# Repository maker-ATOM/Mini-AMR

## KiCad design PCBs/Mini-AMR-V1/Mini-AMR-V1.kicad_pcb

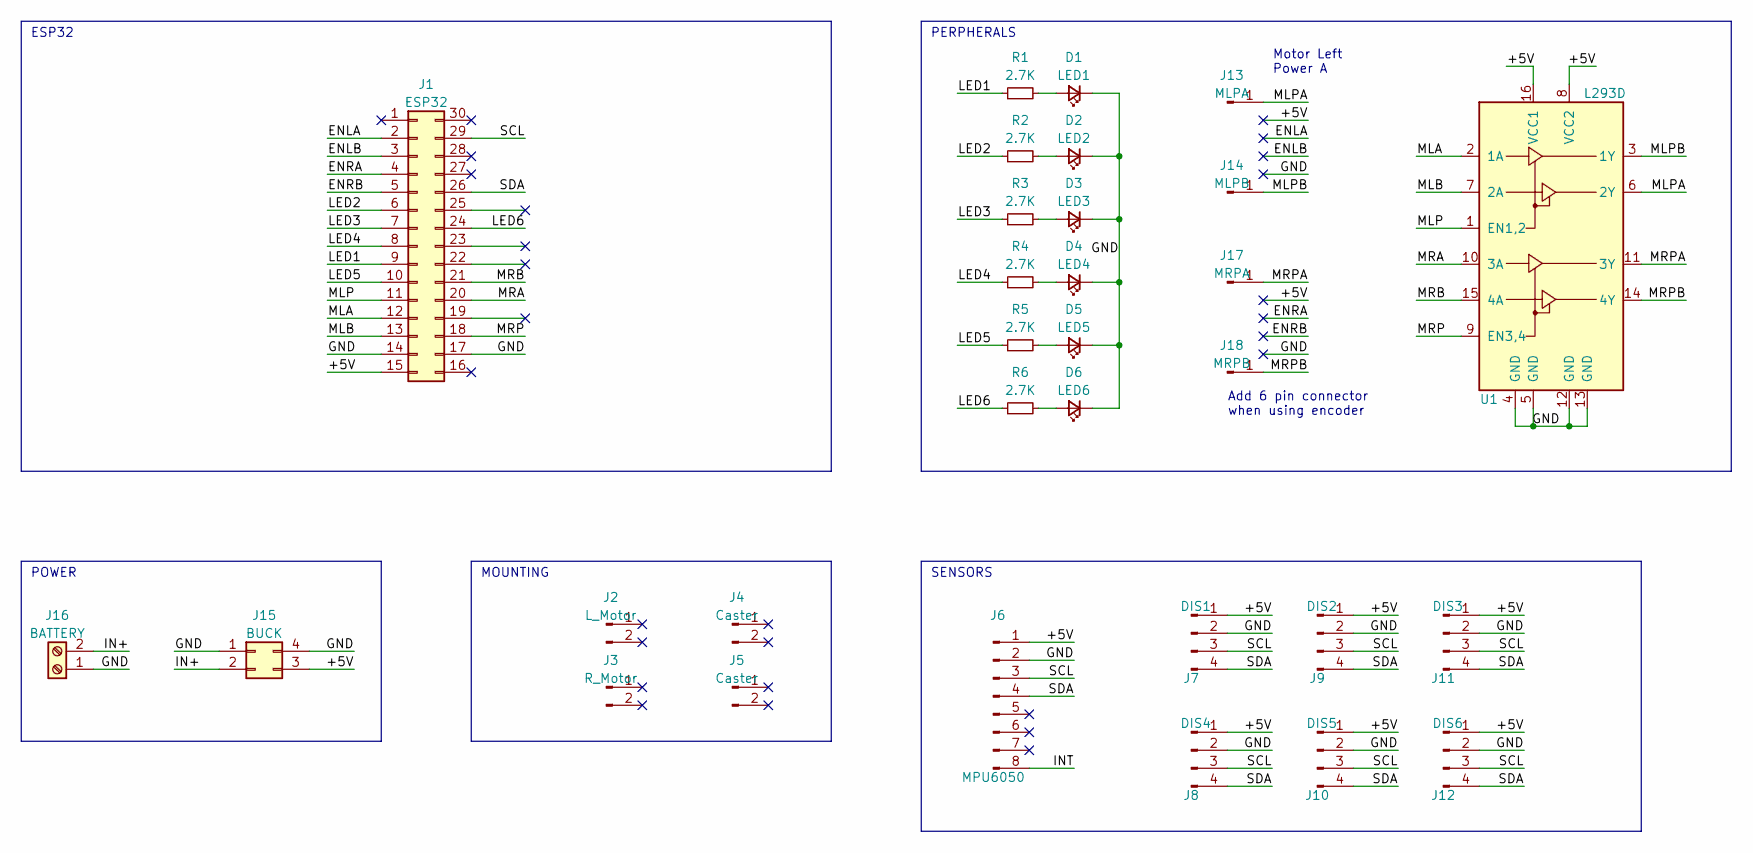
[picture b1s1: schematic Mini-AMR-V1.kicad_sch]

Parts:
D1: LED1; LED_0805_2012Metric_Pad1.15x1.40mm_HandSolder
D2: LED2; LED_0805_2012Metric_Pad1.15x1.40mm_HandSolder
D3: LED3; LED_0805_2012Metric_Pad1.15x1.40mm_HandSolder
D4: LED4; LED_0805_2012Metric_Pad1.15x1.40mm_HandSolder
D5: LED5; LED_0805_2012Metric_Pad1.15x1.40mm_HandSolder
D6: LED6; LED_0805_2012Metric_Pad1.15x1.40mm_HandSolder
J1: ESP32
J2: L_Motor; N20 Motor Sys
J3: R_Motor; N20 Motor Sys
J4, J5: Caster; N20 Ball caster
J6: MPU6050
J7: DIS1; VL53L0X
J8: DIS4; VL53L0X
J9: DIS2; VL53L0X
J10: DIS5; VL53L0X
J11: DIS3; VL53L0X
J12: DIS6; VL53L0X
J13: MLPA; PinHeader_1x01_P2.54mm_Vertical
J14: MLPB; PinHeader_1x01_P2.54mm_Vertical
J15: BUCK; Buck
J16: BATTERY; TerminalBlock_bornier-2_P5.08mm
J17: MRPA; PinHeader_1x01_P2.54mm_Vertical
J18: MRPB; PinHeader_1x01_P2.54mm_Vertical
R1, R2, R3, R4, R5, R6: 2.7K; R_0805_2012Metric_Pad1.20x1.40mm_HandSolder
U1: L293D; SMDIP-16_W11.48mm

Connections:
/+5V: J1.15, J6.1, J7.1, J8.1, J9.1, J10.1, J11.1, J12.1, J15.3, U1.8 (VCC2), U1.16 (VCC1)
/ENLA: J1.2
/ENLB: J1.3
/ENRA: J1.4
/ENRB: J1.5
/GND: D1.1 (K), D2.1 (K), D3.1 (K), D4.1 (K), D5.1 (K), D6.1 (K), J1.14, J1.17, J6.2, J7.2, J8.2, J9.2, J10.2, J11.2, J12.2, J15.1, J15.4, J16.1, U1.4 (GND), U1.5 (GND), U1.12 (GND), U1.13 (GND)
/IN+: J15.2, J16.2
/INT: J6.8
/LED1: J1.9, R1.1
/LED2: J1.6, R2.1
/LED3: J1.7, R3.1
/LED4: J1.8, R4.1
/LED5: J1.10, R5.1
/LED6: J1.24, R6.1
/MLA: J1.12, U1.2 (1A)
/MLB: J1.13, U1.7 (2A)
/MLP: J1.11, U1.1 (EN1,2)
/MLPA: J13.1, U1.6 (2Y)
/MLPB: J14.1, U1.3 (1Y)
/MRA: J1.20, U1.10 (3A)
/MRB: J1.21, U1.15 (4A)
/MRP: J1.18, U1.9 (EN3,4)
/MRPA: J17.1, U1.11 (3Y)
/MRPB: J18.1, U1.14 (4Y)
/SCL: J1.29, J6.3, J7.3, J8.3, J9.3, J10.3, J11.3, J12.3
/SDA: J1.26, J6.4, J7.4, J8.4, J9.4, J10.4, J11.4, J12.4
unnamed: D1.2 (A), R1.2
unnamed: D2.2 (A), R2.2
unnamed: D3.2 (A), R3.2
unnamed: D4.2 (A), R4.2
unnamed: D5.2 (A), R5.2
unnamed: D6.2 (A), R6.2

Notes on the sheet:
SENSORS
Add 6 pin connector when using encoder
ESP32
POWER
PERPHERALS
Motor Left Power A
MOUNTING

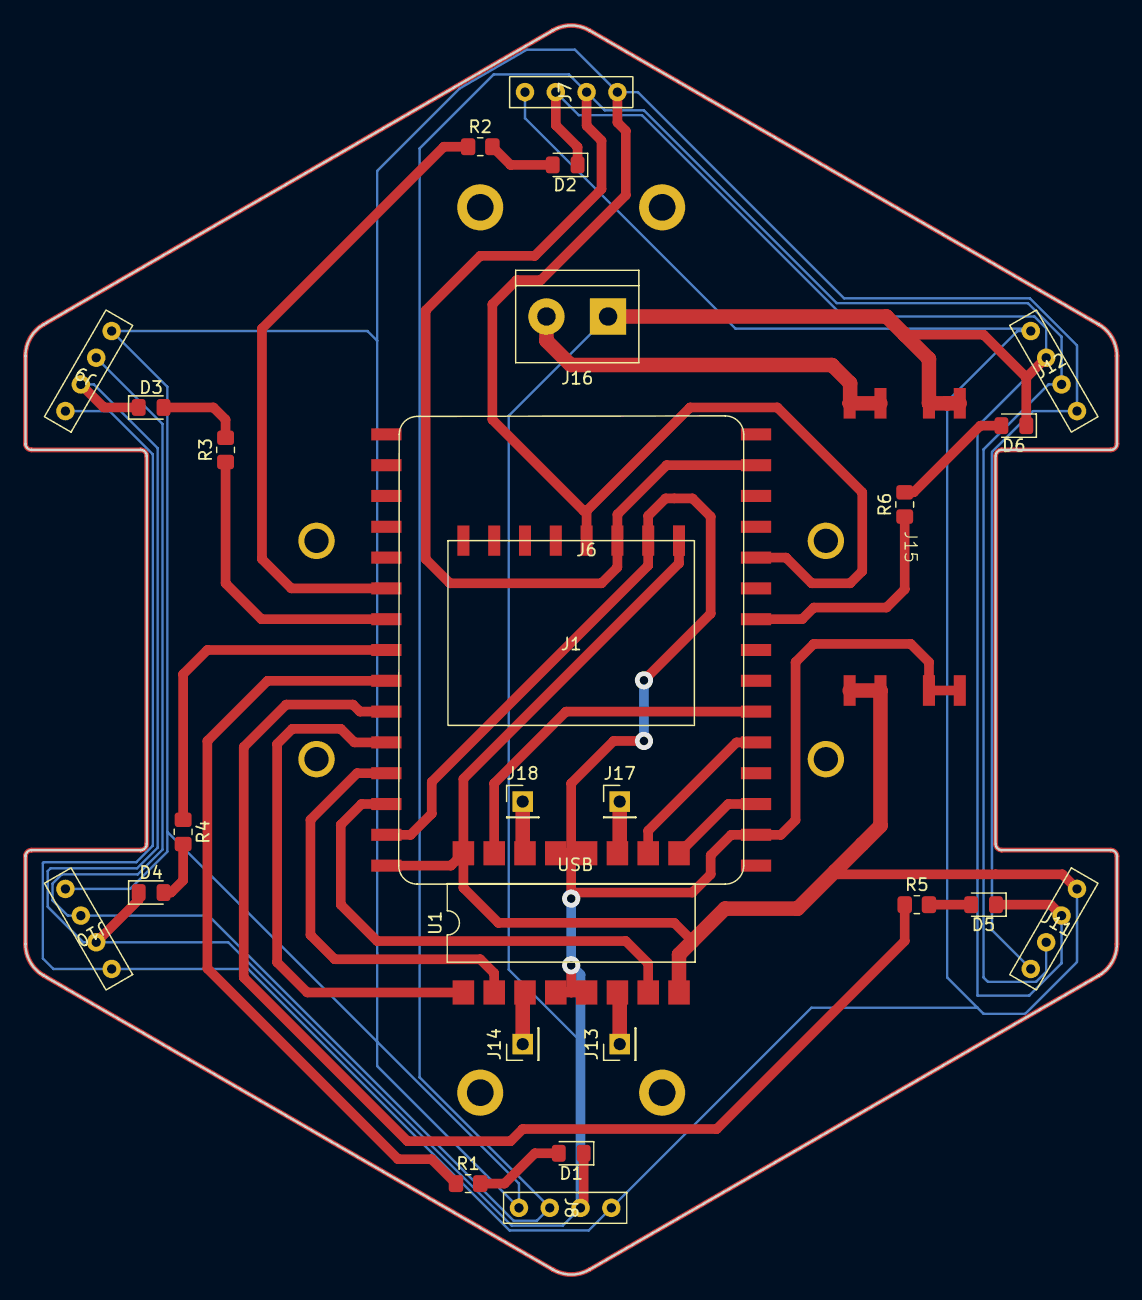
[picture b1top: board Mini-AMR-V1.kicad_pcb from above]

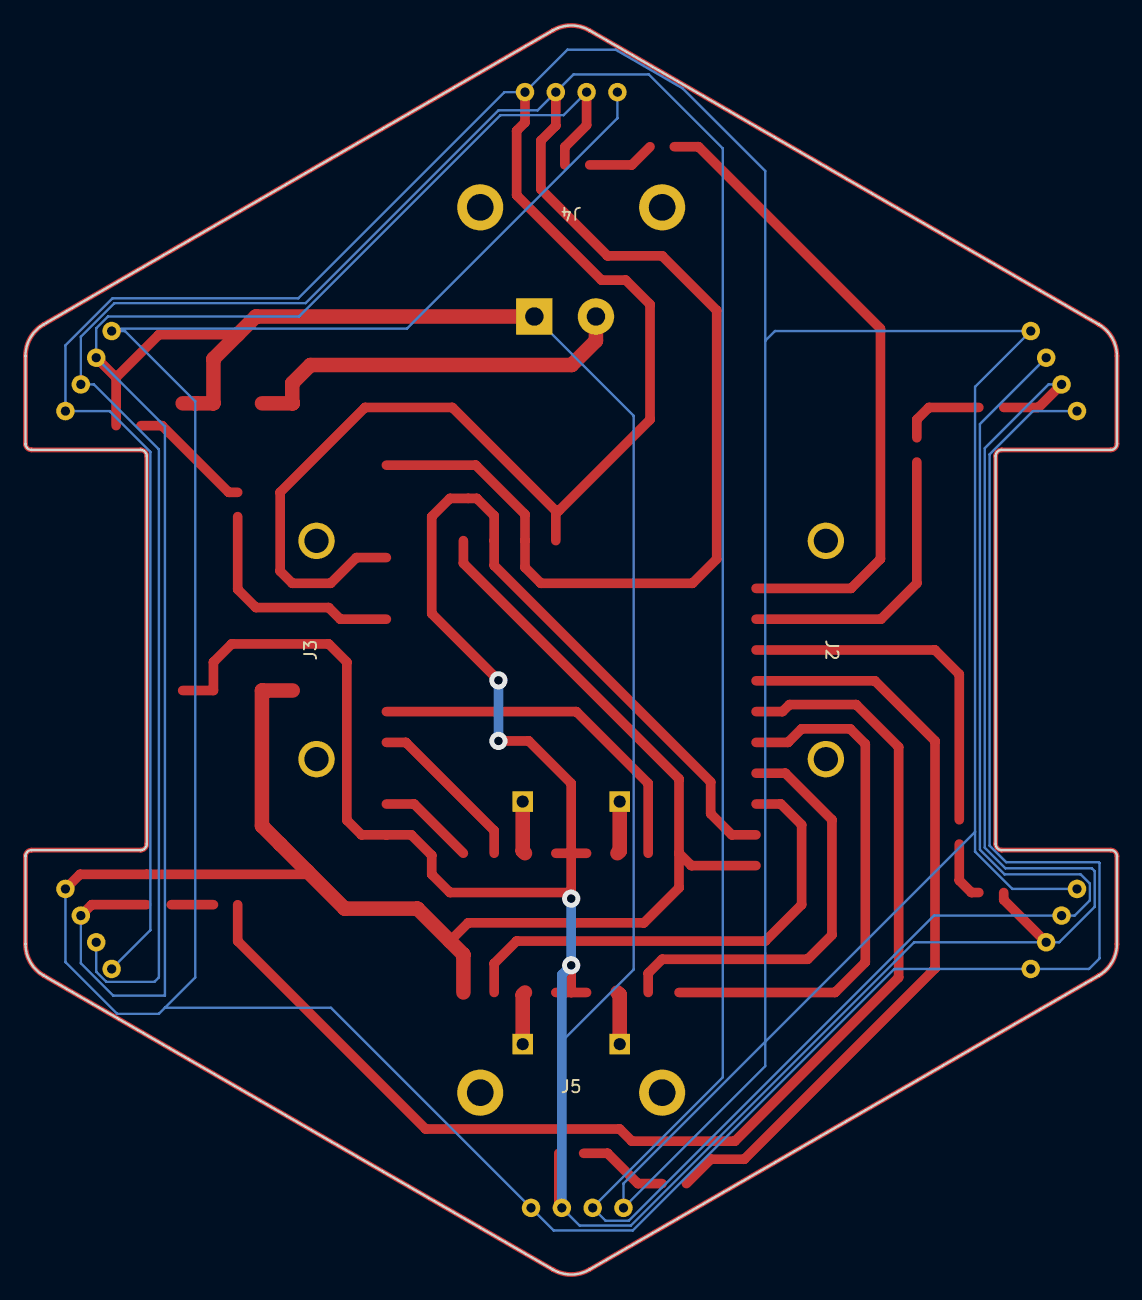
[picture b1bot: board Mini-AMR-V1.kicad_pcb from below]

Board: 2 copper layers, 90.0 x 103.0 mm, 31 parts (4 on the bottom side), 27 nets.

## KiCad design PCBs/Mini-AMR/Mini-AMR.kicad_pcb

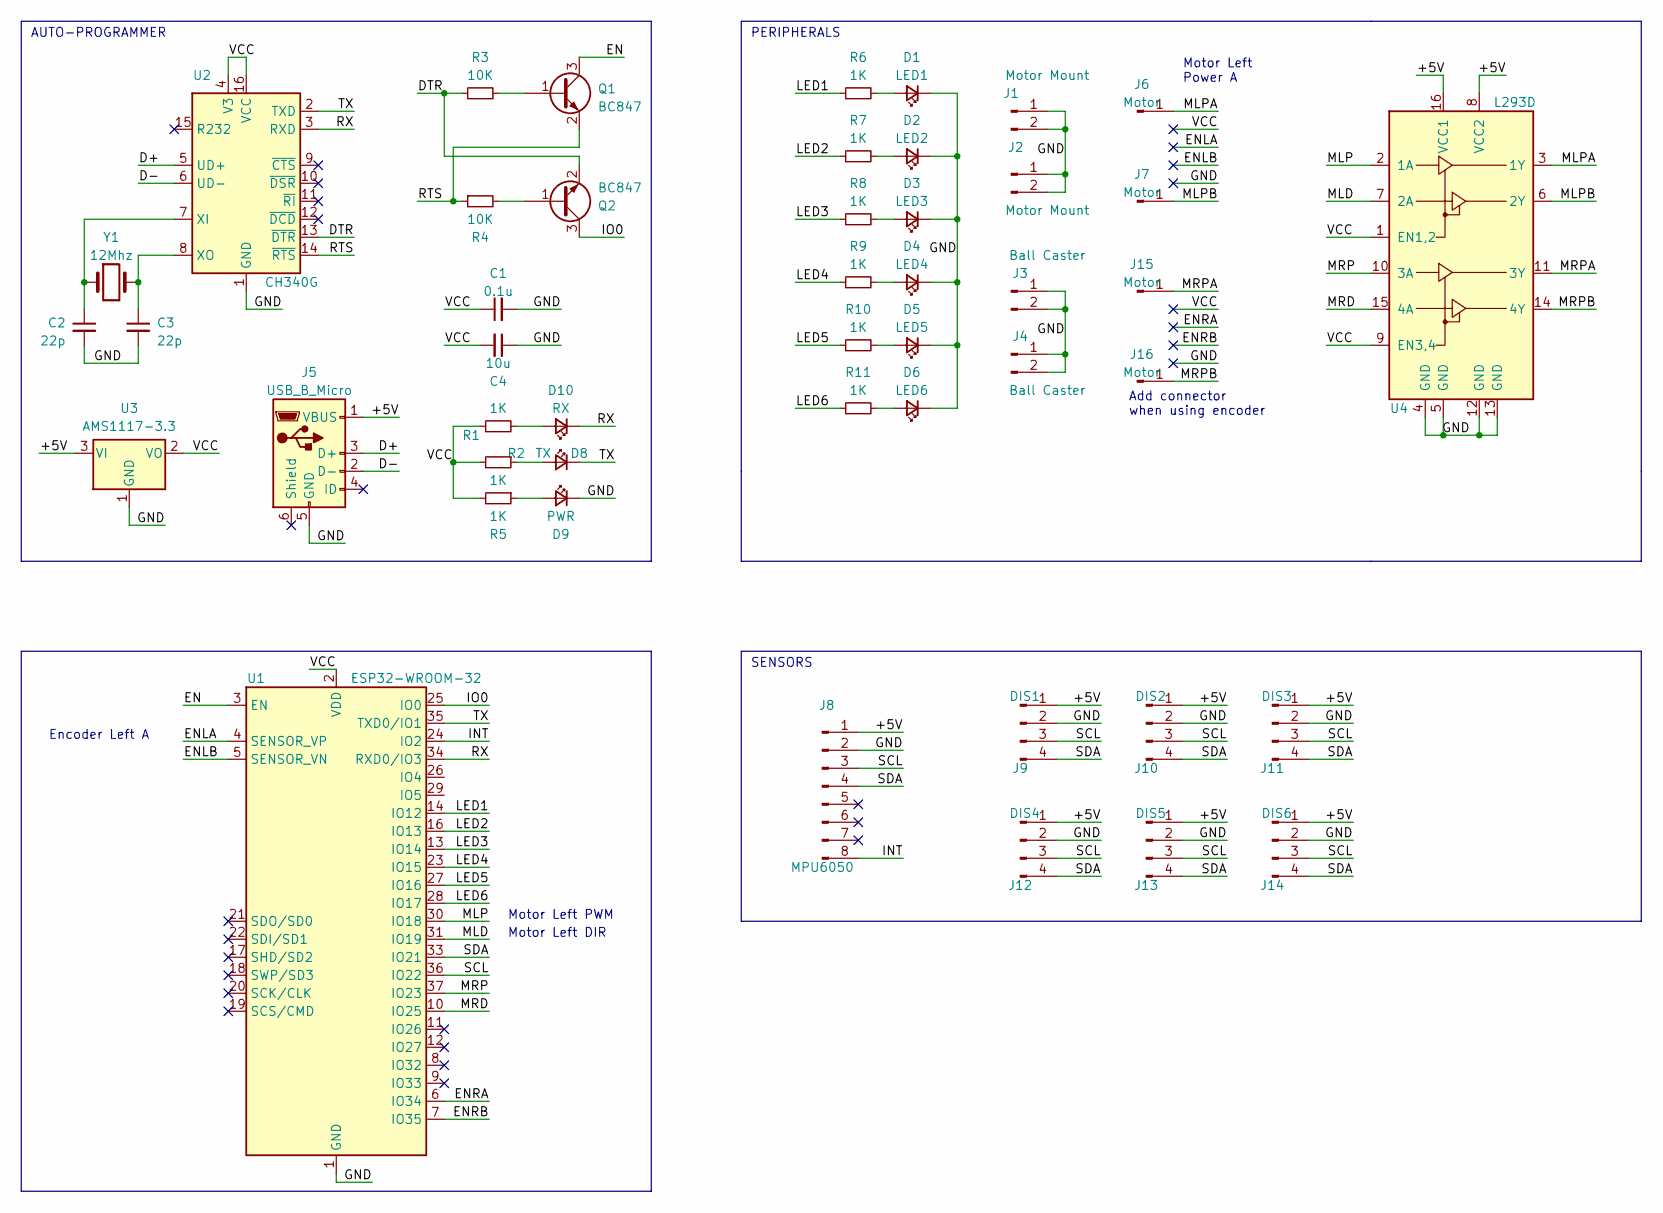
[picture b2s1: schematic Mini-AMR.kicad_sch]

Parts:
C1: 0.1u; C_1206_3216Metric_Pad1.33x1.80mm_HandSolder
C2, C3: 22p; C_0805_2012Metric_Pad1.18x1.45mm_HandSolder
C4: 10u; C_0805_2012Metric_Pad1.18x1.45mm_HandSolder
D1: LED1; LED_0805_2012Metric_Pad1.15x1.40mm_HandSolder
D2: LED2; LED_0805_2012Metric_Pad1.15x1.40mm_HandSolder
D3: LED3; LED_0805_2012Metric_Pad1.15x1.40mm_HandSolder
D4: LED4; LED_0805_2012Metric_Pad1.15x1.40mm_HandSolder
D5: LED5; LED_0805_2012Metric_Pad1.15x1.40mm_HandSolder
D6: LED6; LED_0805_2012Metric_Pad1.15x1.40mm_HandSolder
D8: TX; LED_0805_2012Metric_Pad1.15x1.40mm_HandSolder
D9: PWR; LED_0805_2012Metric_Pad1.15x1.40mm_HandSolder
D10: RX; LED_0805_2012Metric_Pad1.15x1.40mm_HandSolder
J1, J2: Motor Mount; N20 Motor Sys
J3, J4: Ball Caster; N20 Ball caster
J5: USB_B_Micro; USB-micro breakout board
J6, J7, J15, J16: Motor; PinHeader_1x01_P2.54mm_Vertical
J8: MPU6050
J9: DIS1; VL53L0X
J10: DIS2; VL53L0X
J11: DIS3; VL53L0X
J12: DIS4; VL53L0X
J13: DIS5; VL53L0X
J14: DIS6; VL53L0X
Q1, Q2: BC847; SOT-23
R1, R2, R5, R6, R7, R8, R9, R10, R11: 1K; R_0603_1608Metric_Pad0.98x0.95mm_HandSolder
R3, R4: 10K; R_0805_2012Metric_Pad1.20x1.40mm_HandSolder
U1: ESP32-WROOM-32
U2: CH340G; SOIC-16_3.9x9.9mm_P1.27mm
U3: AMS1117-3.3; SOT-223-3_TabPin2
U4: L293D; SMDIP-16_W11.48mm
Y1: 12Mhz; Crystal_SMD_HC49-SD

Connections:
/+5V: J5.1 (VBUS), J8.1, J9.1, J10.1, J11.1, J12.1, J13.1, J14.1, U3.3 (VI), U4.8 (VCC2), U4.16 (VCC1)
/D+: J5.3 (D+), U2.5 (UD+)
/D-: J5.2 (D-), U2.6 (UD-)
/DTR: Q2.2 (E), R3.1, U2.13 (~DTR)
/EN: Q1.3 (C), U1.3 (EN)
/ENLA: U1.4 (SENSOR_VP)
/ENLB: U1.5 (SENSOR_VN)
/ENRA: U1.6 (IO34)
/ENRB: U1.7 (IO35)
/GND: C1.2, C2.2, C3.2, C4.1, D1.1 (K), D2.1 (K), D3.1 (K), D4.1 (K), D5.1 (K), D6.1 (K), D9.1 (K), J1.1, J1.2, J2.1, J2.2, J3.1, J3.2, J4.1, J4.2, J5.5 (GND), J8.2, J9.2, J10.2, J11.2, J12.2, J13.2, J14.2, U1.1 (GND), U1.15 (GND), U1.38 (GND), U1.39 (GND), U2.1 (GND), U3.1 (GND), U4.4 (GND), U4.5 (GND), U4.12 (GND), U4.13 (GND)
/INT: J8.8, U1.24 (IO2)
/IO0: Q2.3 (C), U1.25 (IO0)
/LED1: R6.1, U1.14 (IO12)
/LED2: R7.1, U1.16 (IO13)
/LED3: R8.1, U1.13 (IO14)
/LED4: R9.1, U1.23 (IO15)
/LED5: R10.1, U1.27 (IO16)
/LED6: R11.1, U1.28 (IO17)
/MLD: U1.31 (IO19), U4.7 (2A)
/MLP: U1.30 (IO18), U4.2 (1A)
/MLPA: J6.1, U4.3 (1Y); also elsewhere on the board
/MLPB: J7.1, U4.6 (2Y)
/MRD: U1.10 (IO25), U4.15 (4A)
/MRP: U1.37 (IO23), U4.10 (3A)
/MRPA: J15.1, U4.11 (3Y)
/MRPB: J16.1, U4.14 (4Y)
/RTS: Q1.2 (E), R4.1, U2.14 (~RTS)
/RX: D10.1 (K), U1.34 (RXD0/IO3), U2.3 (RXD)
/SCL: J8.3, J9.3, J10.3, J11.3, J12.3, J13.3, J14.3, U1.36 (IO22)
/SDA: J8.4, J9.4, J10.4, J11.4, J12.4, J13.4, J14.4, U1.33 (IO21)
/TX: D8.1 (K), U1.35 (TXD0/IO1), U2.2 (TXD)
/VCC: C1.1, C4.2, R1.1, R2.2, R5.2, U1.2 (VDD), U2.4 (V3), U2.16 (VCC), U3.2 (VO), U4.1 (EN1,2), U4.9 (EN3,4)
unnamed: D1.2 (A), R6.2
unnamed: D2.2 (A), R7.2
unnamed: D3.2 (A), R8.2
unnamed: D4.2 (A), R9.2
unnamed: D5.2 (A), R10.2
unnamed: D6.2 (A), R11.2
unnamed: D8.2 (A), R2.1
unnamed: D9.2 (A), R5.1
unnamed: D10.2 (A), R1.2
unnamed: Q1.1 (B), R3.2
unnamed: Q2.1 (B), R4.2
unnamed: C2.1, U2.7 (XI), Y1.1
unnamed: C3.1, U2.8 (XO), Y1.2

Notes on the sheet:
PERIPHERALS
Add connector when using encoder
Motor Left Power A
Encoder Left A
Motor Left PWM
SENSORS
Motor Left DIR
AUTO-PROGRAMMER

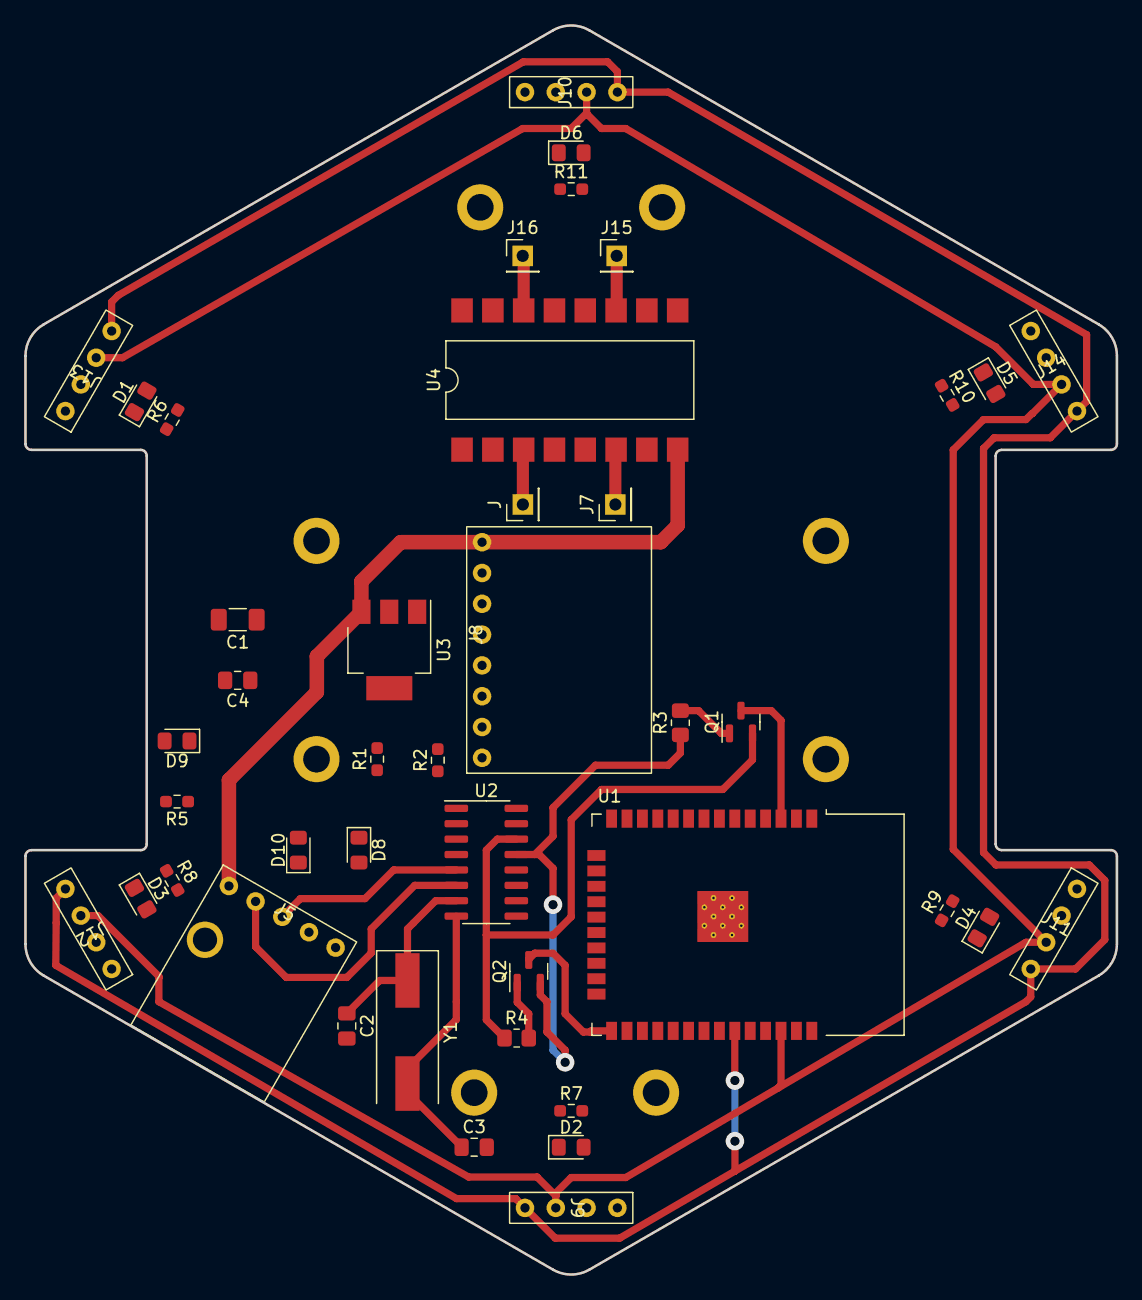
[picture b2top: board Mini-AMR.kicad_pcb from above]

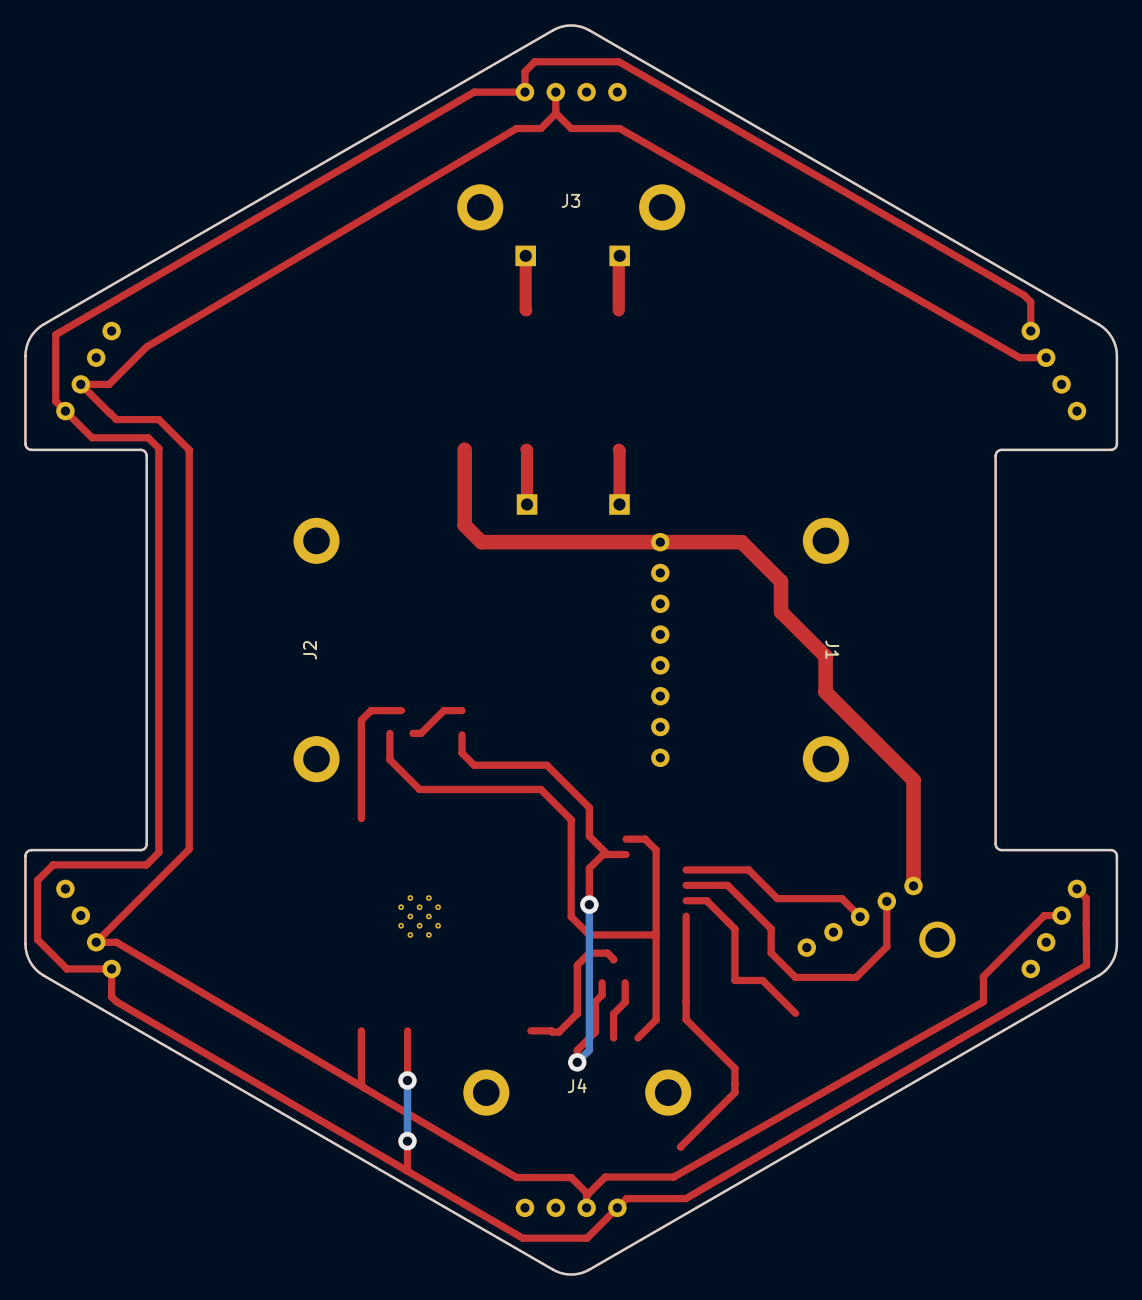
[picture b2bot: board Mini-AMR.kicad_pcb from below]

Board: 2 copper layers, 90.0 x 103.0 mm, 47 parts (4 on the bottom side), 41 nets.

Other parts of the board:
J: Motor; PinHeader_1x01_P2.54mm_Vertical

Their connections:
/MLPA: J.1; also elsewhere on the board

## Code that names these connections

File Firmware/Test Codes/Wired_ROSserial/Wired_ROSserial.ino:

#include <ros.h>
#include <geometry_msgs/Twist.h>


#define MRP 14
#define MRA 12
#define MRB 13
#define MLP 15
#define MLA 4
#define MLB 16

float mlpwm = 0;
byte mldir = 0;
float mrpwm = 0;
byte mrdir = 0;

ros::NodeHandle esp_node;

unsigned long previousMillis = 0;
unsigned long currentMillis = 0;

int ledpwm = 1;
int increment = 1;

void vel_Callback(const geometry_msgs::Twist& vel_data) {
  mlpwm = vel_data.linear.x * 1000 - vel_data.angular.z * 1000;
  mrpwm = vel_data.linear.x * 1000 + vel_data.angular.z * 1000;

  mlpwm = map(mlpwm, -255, 255, -761, 761);  // 0.761 = max robot speed in m/s
  mrpwm = map(mrpwm, -255, 255, -761, 761);  // 0.761 = max robot speed in m/s

  if (mlpwm > 0) {
    mldir = 0;
  } else if (mlpwm < 0) {
    mldir = 1;
    mlpwm = -mlpwm;
  }

  if (mrpwm > 0) {
    mrdir = 0;
  } else if (mrpwm < 0) {
    mrdir = 1;
    mrpwm = -mrpwm;
  }

  mlpwm = constrain(mlpwm, 0, 255);
  mrpwm = constrain(mrpwm, 0, 255);
}

ros::Subscriber<geometry_msgs::Twist> sub("cmd_vel", &vel_Callback);

void setup() {
  pinMode(2, OUTPUT);
  esp_node.initNode();
  esp_node.subscribe(sub);

  ledcSetup(0, 5000, 8);
  ledcAttachPin(32, 0);
  ledcAttachPin(26, 0);


  ledcSetup(1, 5000, 8);
  ledcAttachPin(MLP, 1);
  ledcAttachPin(33, 1);
  ledcAttachPin(25, 1);
  ledcSetup(2, 5000, 8);
  ledcAttachPin(MRP, 2);
  ledcAttachPin(18, 2);
  ledcAttachPin(27, 2);
  pinMode(MLA, OUTPUT);
  pinMode(MLB, OUTPUT);
  pinMode(MRA, OUTPUT);
  pinMode(MRB, OUTPUT);
}

void loop() {

  ledcWrite(1, mlpwm);

  digitalWrite(MLA, mldir);
  digitalWrite(MLB, !mldir);
  ledcWrite(2, mrpwm);
  digitalWrite(MRA, mrdir);
  digitalWrite(MRB, !mrdir);

  esp_node.spinOnce();
  currentMillis = millis();
  if (currentMillis - previousMillis >= 10) {
    ledPattern();
    previousMillis = currentMillis;
  }
}

void ledPattern() {
  if (ledpwm > 120 || ledpwm < 1) {
    increment *= -1;
  }
  ledpwm += increment;

  ledcWrite(0, ledpwm);
}

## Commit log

2023-07-09 Wired ROSserial ready
2023-08-08 latest push
